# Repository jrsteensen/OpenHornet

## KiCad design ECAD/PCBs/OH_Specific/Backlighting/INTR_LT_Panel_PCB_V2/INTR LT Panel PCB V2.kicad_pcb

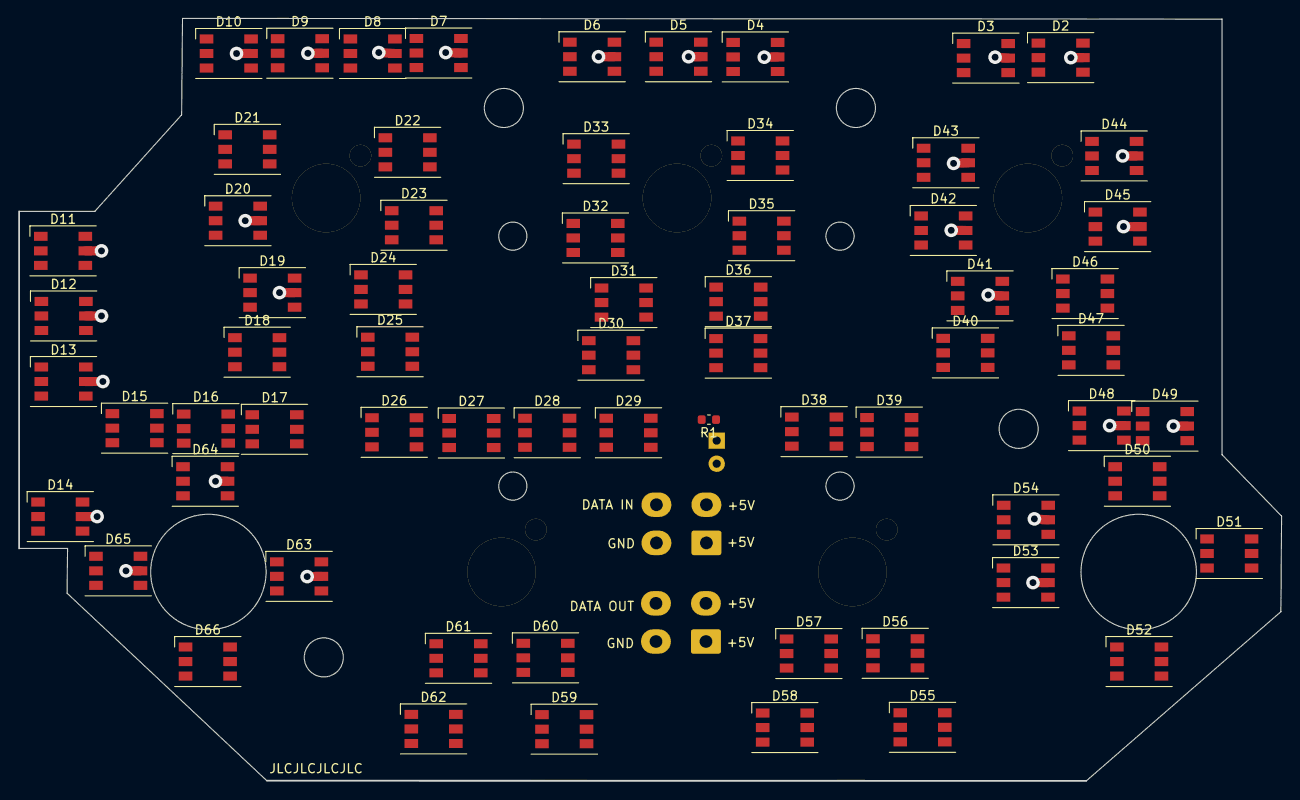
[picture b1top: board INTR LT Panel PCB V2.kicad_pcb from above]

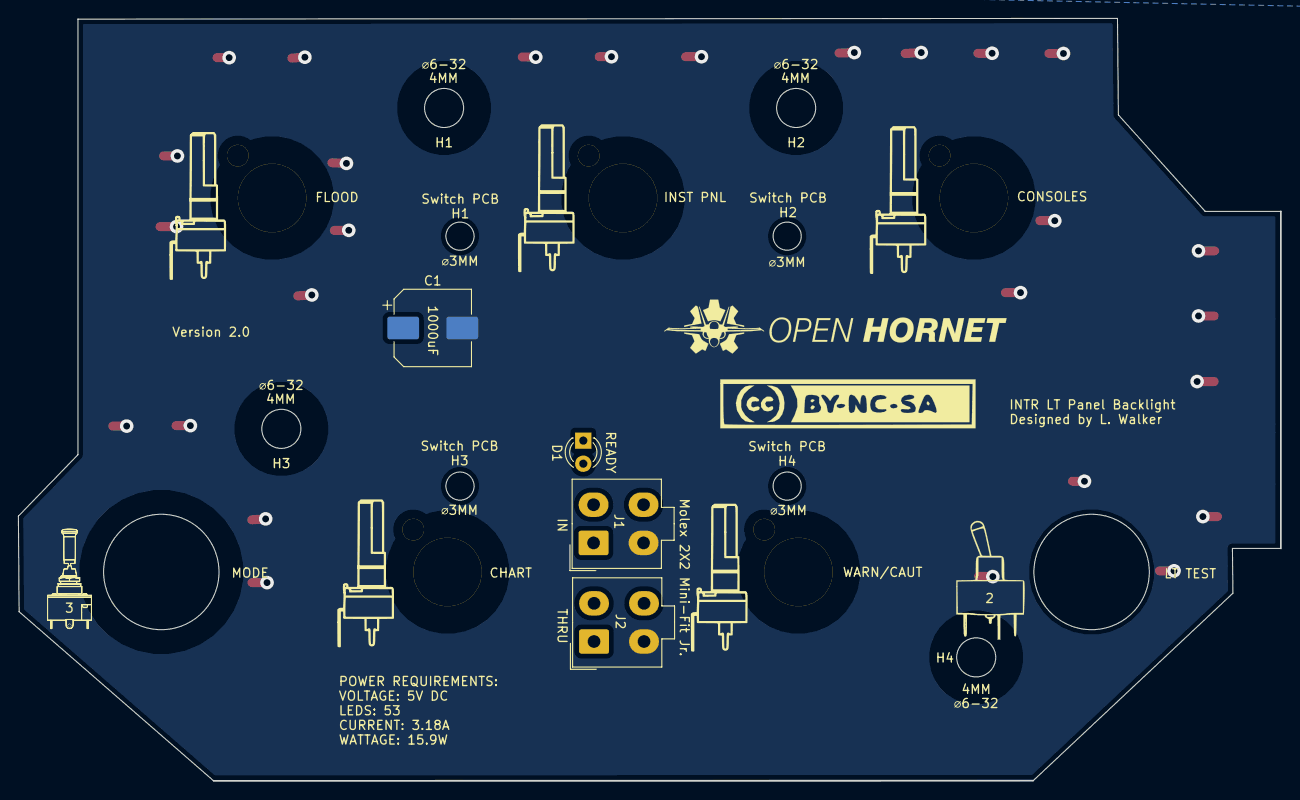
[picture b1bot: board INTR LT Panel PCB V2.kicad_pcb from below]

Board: 2 copper layers, 138.9 x 83.9 mm, 90 parts (13 on the bottom side), 68 nets.

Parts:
1, 2, 3, 4: OH_Panel_Fastner_Keepout; OH_Panel_6-32_PHS
5, 6, 7, 9, 10: BR10K_Pot_11mm_x_11mm
8: 631H_Toggle_13mm_x_13mm
11: SxAL_Toggle_13x13mm
C1: C_Polarized; CP_Elec_8x10
D1: LED; LED_D3.0mm
D2, D3, D4, D5, D6, D7, D8, D9, D10, D11, D12, D13, D14, D15, D16, D17, D18, D19, D20, D21, D22, D23, D24, D25, D26, D27, D28, D29, D30, D31, D32, D33, D34, D35, D36, D37, D38, D39, D40, D41, D42, D43, D44, D45, D46, D47, D48, D49, D50, D51, D52, D53, D54, D55, D56, D57, D58, D59, D60, D61, D62, D63, D64, D65, D66: WS2812B; LED_WS2812_PLCC6_5.0x5.0mm_P1.6mm
G1: LOGO; 631HToggle
G2, G3, G4, G6, G7: LOGO; BR10K_Pot_Silkscreen
G5: LOGO; S3ALToggle
G8: LOGO; OH_LOGO_37.7mm_5.9mm
G9: LOGO; CC-BY-NC-SA-Small
J1, J2: Conn_01x04_Female; Molex_Mini-Fit_Jr_5566-04A_2x02_P4.20mm_Vertical
R1: R; R_0603_1608Metric

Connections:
/DATAIN: D2.4, D2.6, D3.6, J1.4
/DATAOUT: D66.3, J2.4
/LED+5V: C1.1, D1.2, D2.1, D2.2, D3.1, D3.2, D4.1, D4.2, D5.1, D5.2, D6.1, D6.2, D7.1, D7.2, D8.1, D8.2, D9.1, D9.2, D10.1, D10.2, D11.1, D11.2, D12.1, D12.2, D13.1, D13.2, D14.1, D14.2, D15.1, D15.2, D16.1, D16.2, D17.1, D17.2, D18.1, D18.2, D19.1, D19.2, D20.1, D20.2, D21.1, D21.2, D22.1, D22.2, D23.1, D23.2, D24.1, D24.2, D25.1, D25.2, D26.1, D26.2, D27.1, D27.2, D28.1, D28.2, D29.1, D29.2, D30.1, D30.2, D31.1, D31.2, D32.1, D32.2, D33.1, D33.2, D34.1, D34.2, D35.1, D35.2, D36.1, D36.2, D37.1, D37.2, D38.1, D38.2, D39.1, D39.2, D40.1, D40.2, D41.1, D41.2, D42.1, D42.2, D43.1, D43.2, D44.1, D44.2, D45.1, D45.2, D46.1, D46.2, D47.1, D47.2, D48.1, D48.2, D49.1, D49.2, D50.1, D50.2, D51.1, D51.2, D52.1, D52.2, D53.1, D53.2, D54.1, D54.2, D55.1, D55.2, D56.1, D56.2, D57.1, D57.2, D58.1, D58.2, D59.1, D59.2, D60.1, D60.2, D61.1, D61.2, D62.1, D62.2, D63.1, D63.2, D64.1, D64.2, D65.1, D65.2, D66.1, D66.2, J1.1, J1.2, J2.1, J2.2
/LEDGND: C1.2, D2.5, D3.5, D4.5, D5.5, D6.5, D7.5, D8.5, D9.5, D10.5, D11.5, D12.5, D13.5, D14.5, D15.5, D16.5, D17.5, D18.5, D19.5, D20.5, D21.5, D22.5, D23.5, D24.5, D25.5, D26.5, D27.5, D28.5, D29.5, D30.5, D31.5, D32.5, D33.5, D34.5, D35.5, D36.5, D37.5, D38.5, D39.5, D40.5, D41.5, D42.5, D43.5, D44.5, D45.5, D46.5, D47.5, D48.5, D49.5, D50.5, D51.5, D52.5, D53.5, D54.5, D55.5, D56.5, D57.5, D58.5, D59.5, D60.5, D61.5, D62.5, D63.5, D64.5, D65.5, D66.5, J1.3, J2.3, R1.2
unnamed: D1.1, R1.1
unnamed: D2.3, D3.4, D4.6
unnamed: D3.3, D4.4, D5.6
unnamed: D4.3, D5.4, D6.6
unnamed: D5.3, D6.4, D7.6
unnamed: D6.3, D7.4, D8.6
unnamed: D7.3, D8.4, D9.6
unnamed: D10.3, D11.4, D12.6
unnamed: D9.3, D10.4, D11.6
unnamed: D8.3, D9.4, D10.6
unnamed: D11.3, D12.4, D13.6
unnamed: D12.3, D13.4, D14.6
unnamed: D13.3, D14.4, D15.6
unnamed: D14.3, D15.4, D16.6
unnamed: D15.3, D16.4, D17.6
unnamed: D16.3, D17.4, D18.6
unnamed: D17.3, D18.4, D19.6
unnamed: D18.3, D19.3, D19.4, D20.4, D21.6
unnamed: D20.3, D21.4, D22.6
unnamed: D21.3, D22.4, D23.6
unnamed: D22.3, D23.4, D24.6
unnamed: D23.3, D24.4, D25.6
unnamed: D24.3, D25.4, D26.6
unnamed: D25.3, D26.4, D27.6
unnamed: D26.3, D27.4, D28.6
unnamed: D27.3, D28.4, D29.6
unnamed: D28.3, D29.4, D30.6
unnamed: D29.3, D30.4, D31.6
unnamed: D30.3, D31.4, D32.6
unnamed: D31.3, D32.4, D33.6
unnamed: D32.3, D33.4, D34.6
unnamed: D33.3, D34.4, D35.6
unnamed: D34.3, D35.4, D36.6
unnamed: D35.3, D36.4, D37.6
unnamed: D36.3, D37.4, D38.6
unnamed: D37.3, D38.4, D39.6
unnamed: D38.3, D39.4, D40.6
unnamed: D39.3, D40.4, D41.6
unnamed: D40.3, D41.4, D42.6
unnamed: D41.3, D42.4, D43.6
unnamed: D42.3, D43.4, D44.6
unnamed: D43.3, D44.4, D45.6
unnamed: D44.3, D45.4, D46.6
unnamed: D45.3, D46.4, D47.6
unnamed: D46.3, D47.4, D48.6
unnamed: D47.3, D48.4, D49.6
unnamed: D48.3, D49.4, D50.6
unnamed: D49.3, D50.4, D51.6
unnamed: D50.3, D51.4, D52.6
unnamed: D51.3, D52.4, D53.6
unnamed: D52.3, D53.4, D54.6
unnamed: D53.3, D54.4, D55.6
unnamed: D54.3, D55.4, D56.6
unnamed: D55.3, D56.4, D57.6
unnamed: D56.3, D57.4, D58.6
unnamed: D57.3, D58.4, D59.6
unnamed: D58.3, D59.4, D60.6
unnamed: D59.3, D60.4, D61.6
unnamed: D60.3, D61.4, D62.6
unnamed: D61.3, D62.4, D63.6
unnamed: D62.3, D63.4, D64.6
unnamed: D63.3, D64.4, D65.6
unnamed: D64.3, D65.4, D66.6
unnamed: D65.3, D66.4

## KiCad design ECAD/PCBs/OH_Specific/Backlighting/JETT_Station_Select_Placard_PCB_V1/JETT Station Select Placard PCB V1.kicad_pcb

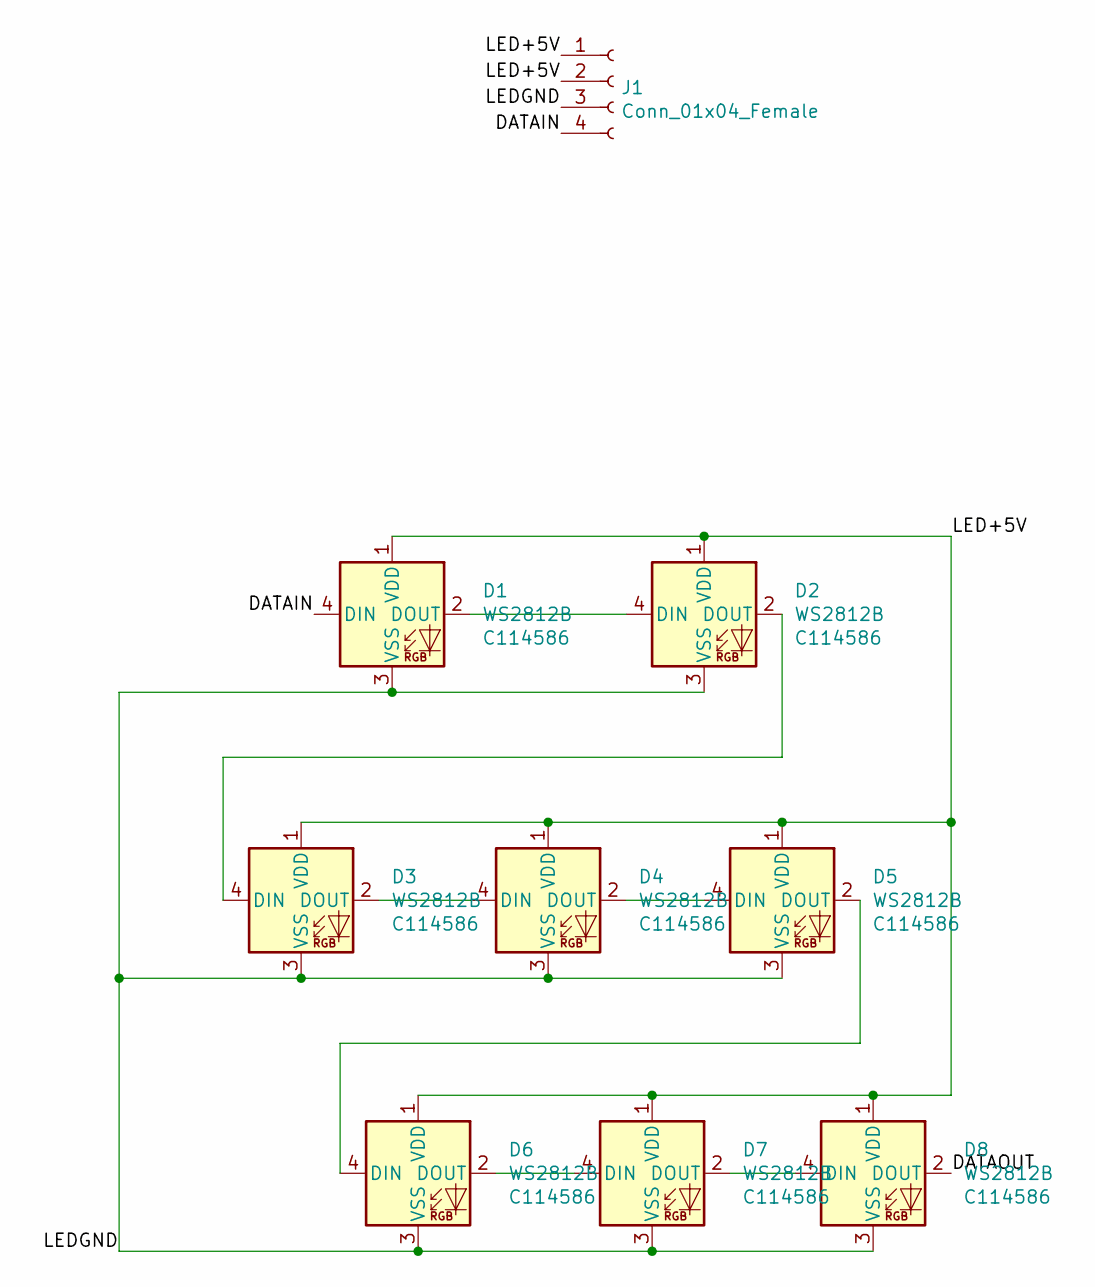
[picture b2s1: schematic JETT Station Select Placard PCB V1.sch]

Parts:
D1, D2, D3, D4, D5, D6, D7, D8: WS2812B; LED_WS2812B_PLCC4_5.0x5.0mm_P3.2mm; LCSC Part Number C114586
J1: Conn_01x04_Female; Molex_Mini-Fit_Jr_5566-04A_2x02_P4.20mm_Vertical

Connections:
/DATAIN: D1.4 (DIN), J1.4
/DATAOUT: D8.2 (DOUT)
/LED+5V: D1.1 (VDD), D2.1 (VDD), D3.1 (VDD), D4.1 (VDD), D5.1 (VDD), D6.1 (VDD), D7.1 (VDD), D8.1 (VDD), J1.1, J1.2
/LEDGND: D1.3 (VSS), D2.3 (VSS), D3.3 (VSS), D4.3 (VSS), D5.3 (VSS), D6.3 (VSS), D7.3 (VSS), D8.3 (VSS), J1.3
unnamed: D1.2 (DOUT), D2.4 (DIN)
unnamed: D2.2 (DOUT), D3.4 (DIN)
unnamed: D3.2 (DOUT), D4.4 (DIN)
unnamed: D4.2 (DOUT), D5.4 (DIN)
unnamed: D5.2 (DOUT), D6.4 (DIN)
unnamed: D6.2 (DOUT), D7.4 (DIN)
unnamed: D7.2 (DOUT), D8.4 (DIN)

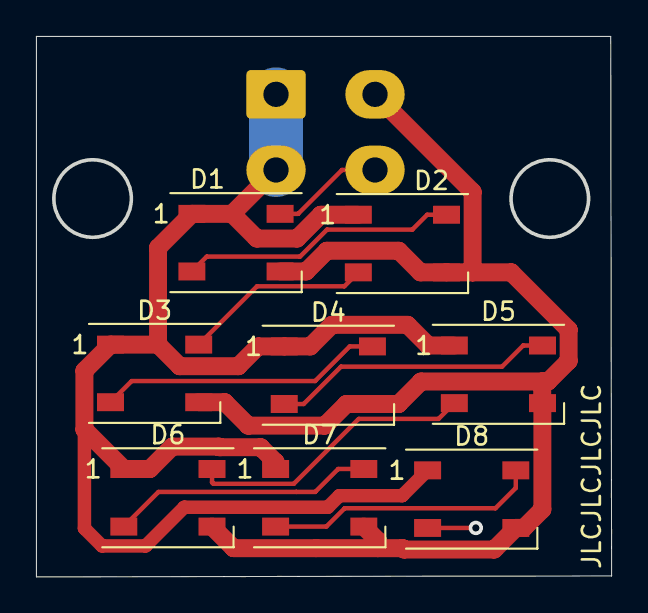
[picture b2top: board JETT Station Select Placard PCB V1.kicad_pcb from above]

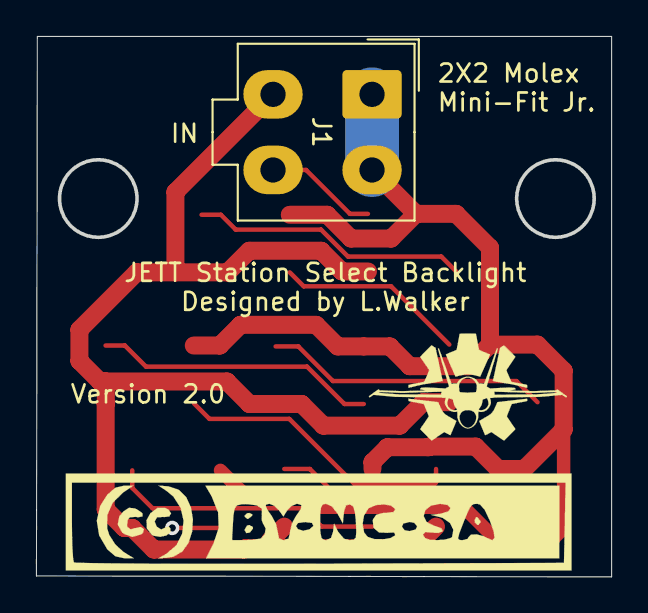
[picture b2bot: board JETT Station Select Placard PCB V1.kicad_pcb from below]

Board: 2 copper layers, 32.0 x 30.0 mm, 11 parts (3 on the bottom side), 10 nets.

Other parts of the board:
G1: OH_LOGO_ONLY_11x6mm
G2: LOGO; CC-BY-NC-SA-Small

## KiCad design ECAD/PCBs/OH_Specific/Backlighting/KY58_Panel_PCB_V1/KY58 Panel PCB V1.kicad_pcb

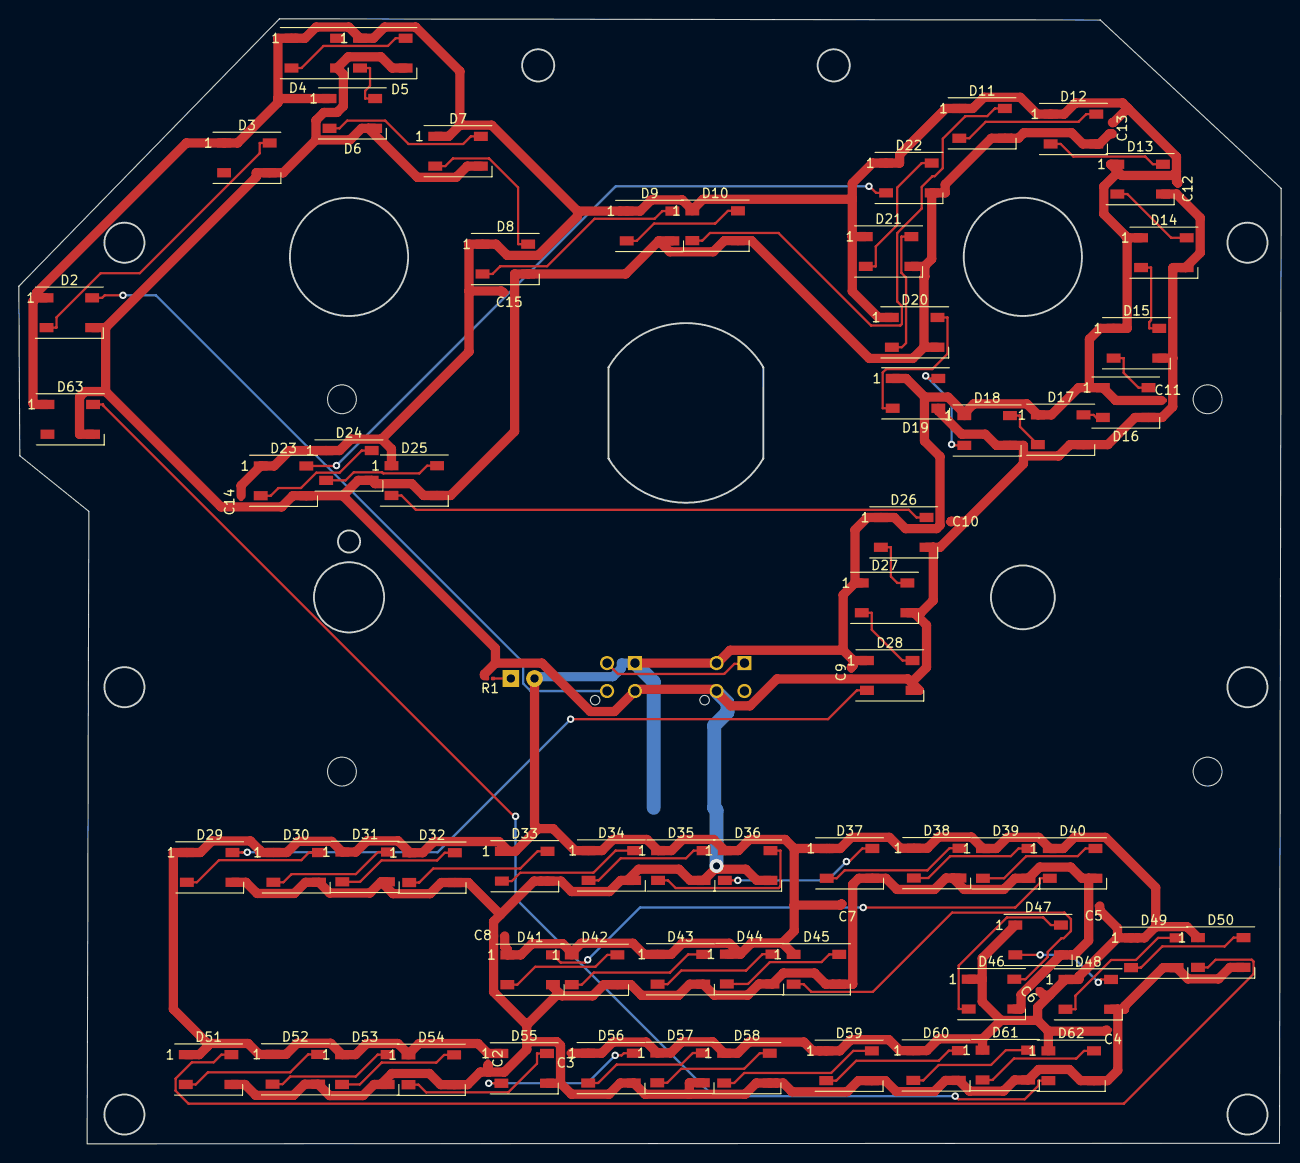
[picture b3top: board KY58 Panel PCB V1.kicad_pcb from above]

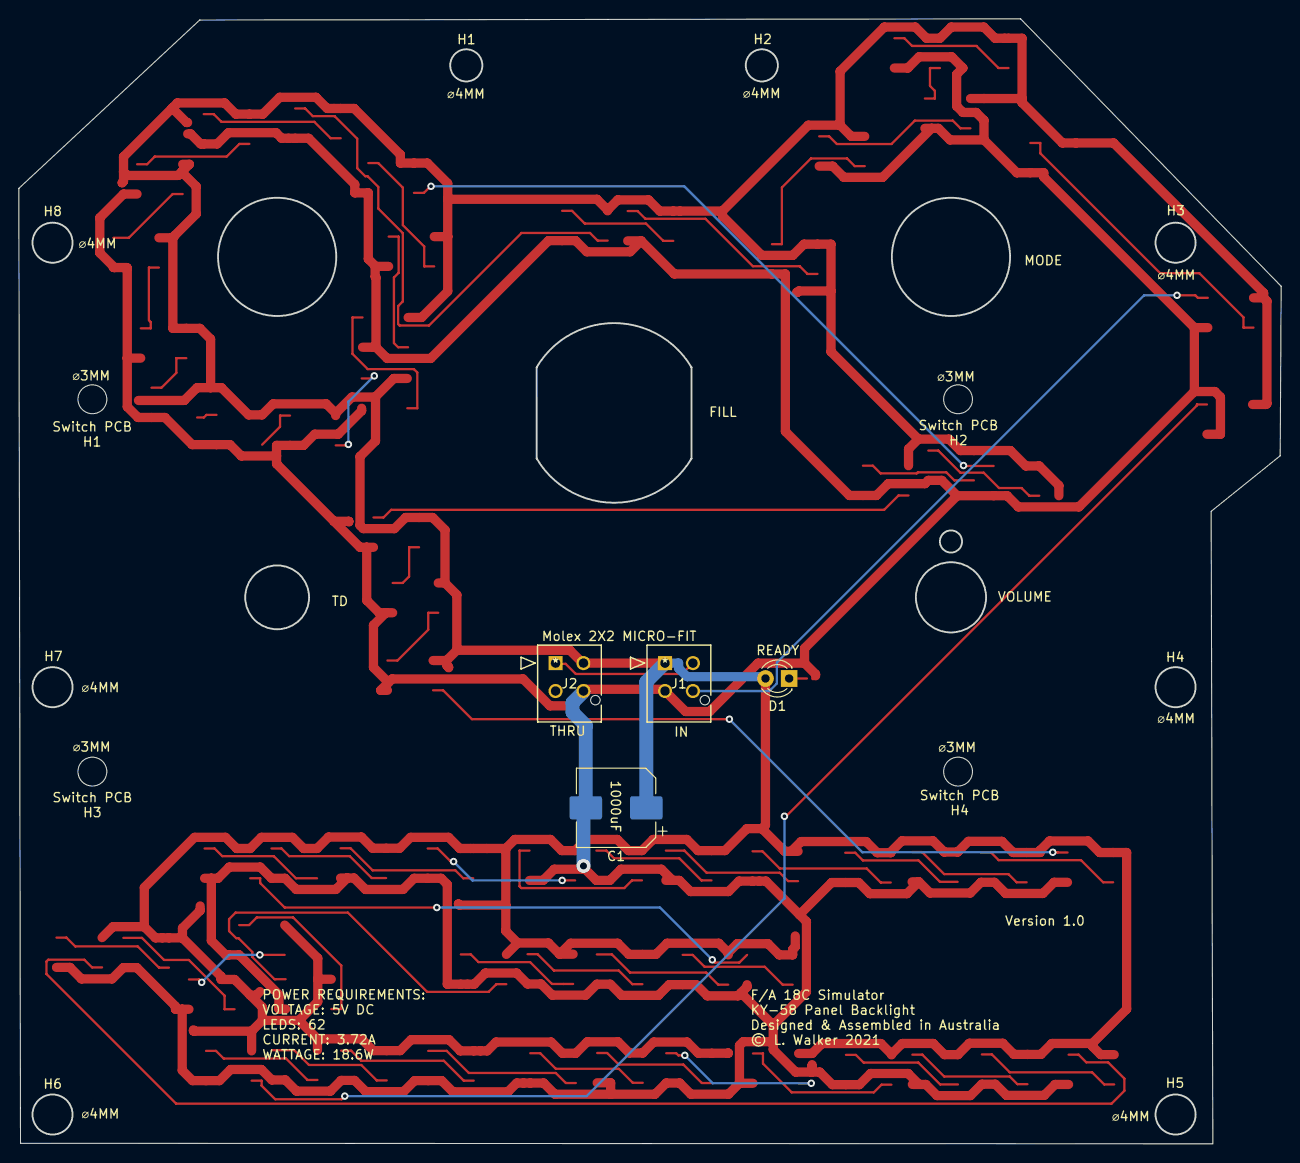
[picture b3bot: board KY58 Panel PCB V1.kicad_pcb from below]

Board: 2 copper layers, 135.6 x 120.9 mm, 81 parts (4 on the bottom side), 65 nets.

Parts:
C1: C_Polarized; CP_Elec_8x10
C2, C3, C4, C5, C6, C7, C8, C9, C10, C11, C12, C13, C14, C15: C; C_0201_0603Metric
D1: LED; LED_D3.0mm
D2, D3, D4, D5, D6, D7, D8, D9, D10, D11, D12, D13, D14, D15, D16, D17, D18, D19, D20, D21, D22, D23, D24, D25, D26, D27, D28, D29, D30, D31, D32, D33, D34, D35, D36, D37, D38, D39, D40, D41, D42, D43, D44, D45, D46, D47, D48, D49, D50, D51, D52, D53, D54, D55, D56, D57, D58, D59, D60, D61, D62, D63: WS2812B; LED_WS2812B_PLCC4_5.0x5.0mm_P3.2mm
J1, J2: Conn_01x04_Female; Molex_MicroFit_2X2
R1: R; R_0201_0603Metric

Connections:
/DATAIN: D2.4, J1.4
/DATALOOP: J1.2, J2.1
/DATAOUT1: D25.2, D26.4
/DATAOUT2: D49.2, D50.4
/LED+5V: C1.1, C2.1, C3.1, C4.1, C5.1, C6.1, C7.1, C8.1, C9.1, C10.1, C11.1, C12.1, C13.1, C14.1, C15.1, D1.2, D2.1, D3.1, D4.1, D5.1, D6.1, D7.1, D8.1, D9.1, D10.1, D11.1, D12.1, D13.1, D14.1, D15.1, D16.1, D17.1, D18.1, D19.1, D20.1, D21.1, D22.1, D23.1, D24.1, D25.1, D26.1, D27.1, D28.1, D29.1, D30.1, D31.1, D32.1, D33.1, D34.1, D35.1, D36.1, D37.1, D38.1, D39.1, D40.1, D41.1, D42.1, D43.1, D44.1, D45.1, D46.1, D47.1, D48.1, D49.1, D50.1, D51.1, D52.1, D53.1, D54.1, D55.1, D56.1, D57.1, D58.1, D59.1, D60.1, D61.1, D62.1, D63.1, J1.1, J2.2
/LEDGND: C1.2, C2.2, C3.2, C4.2, C5.2, C6.2, C7.2, C8.2, C9.2, C10.2, C11.2, C12.2, C13.2, C14.2, C15.2, D2.3, D3.3, D4.3, D5.3, D6.3, D7.3, D8.3, D9.3, D10.3, D11.3, D12.3, D13.3, D14.3, D15.3, D16.3, D17.3, D18.3, D19.3, D20.3, D21.3, D22.3, D23.3, D24.3, D25.3, D26.3, D27.3, D28.3, D29.3, D30.3, D31.3, D32.3, D33.3, D34.3, D35.3, D36.3, D37.3, D38.3, D39.3, D40.3, D41.3, D42.3, D43.3, D44.3, D45.3, D46.3, D47.3, D48.3, D49.3, D50.3, D51.3, D52.3, D53.3, D54.3, D55.3, D56.3, D57.3, D58.3, D59.3, D60.3, D61.3, D62.3, D63.3, J1.3, J2.4, R1.2
unnamed: D1.1, R1.1
unnamed: D2.2, D3.4
unnamed: D4.2, D5.4
unnamed: D5.2, D6.4
unnamed: D6.2, D7.4
unnamed: D7.2, D8.4
unnamed: D8.2, D9.4
unnamed: D10.2, D11.4
unnamed: D9.2, D10.4
unnamed: D11.2, D12.4
unnamed: D12.2, D13.4
unnamed: D13.2, D14.4
unnamed: D14.2, D15.4
unnamed: D15.2, D16.4
unnamed: D16.2, D17.4
unnamed: D17.2, D18.4
unnamed: D18.2, D19.4
unnamed: D19.2, D20.4
unnamed: D20.2, D21.4
unnamed: D21.2, D22.4
unnamed: D22.2, D23.4
unnamed: D23.2, D24.4
unnamed: D24.2, D25.4
unnamed: D26.2, D27.4
unnamed: D27.2, D28.4
unnamed: D28.2, D29.4
unnamed: D29.2, D30.4
unnamed: D30.2, D31.4
unnamed: D31.2, D32.4
unnamed: D32.2, D33.4
unnamed: D33.2, D34.4
unnamed: D34.2, D35.4
unnamed: D35.2, D36.4
unnamed: D36.2, D37.4
unnamed: D37.2, D38.4
unnamed: D38.2, D39.4
unnamed: D39.2, D40.4
unnamed: D40.2, D41.4
unnamed: D41.2, D42.4
unnamed: D42.2, D43.4
unnamed: D43.2, D44.4
unnamed: D44.2, D45.4
unnamed: D45.2, D46.4
unnamed: D46.2, D47.4
unnamed: D47.2, D48.4
unnamed: D48.2, D49.4
unnamed: D50.2, D51.4
unnamed: D51.2, D52.4
unnamed: D52.2, D53.4
unnamed: D53.2, D54.4
unnamed: D54.2, D55.4
unnamed: D55.2, D56.4
unnamed: D56.2, D57.4
unnamed: D57.2, D58.4
unnamed: D58.2, D59.4
unnamed: D59.2, D60.4
unnamed: D60.2, D61.4
unnamed: D61.2, D62.4
unnamed: D62.2, D63.4

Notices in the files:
ECAD/PCBs/OH_Specific/Backlighting/KY58_Panel_PCB_V1/KY58 Panel PCB V1.kicad_pcb:
© L. Walker 2021
parts and their libraries:
Copyright 2016 Accelerated Designs. All rights reserved.
